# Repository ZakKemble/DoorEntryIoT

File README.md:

IoT and a Door Entry System
===========================

Adding IoT to an old apartment entry system.

https://blog.zakkemble.net/iot-and-a-door-entry-system/

---

Zak Kemble

contact@zakkemble.net

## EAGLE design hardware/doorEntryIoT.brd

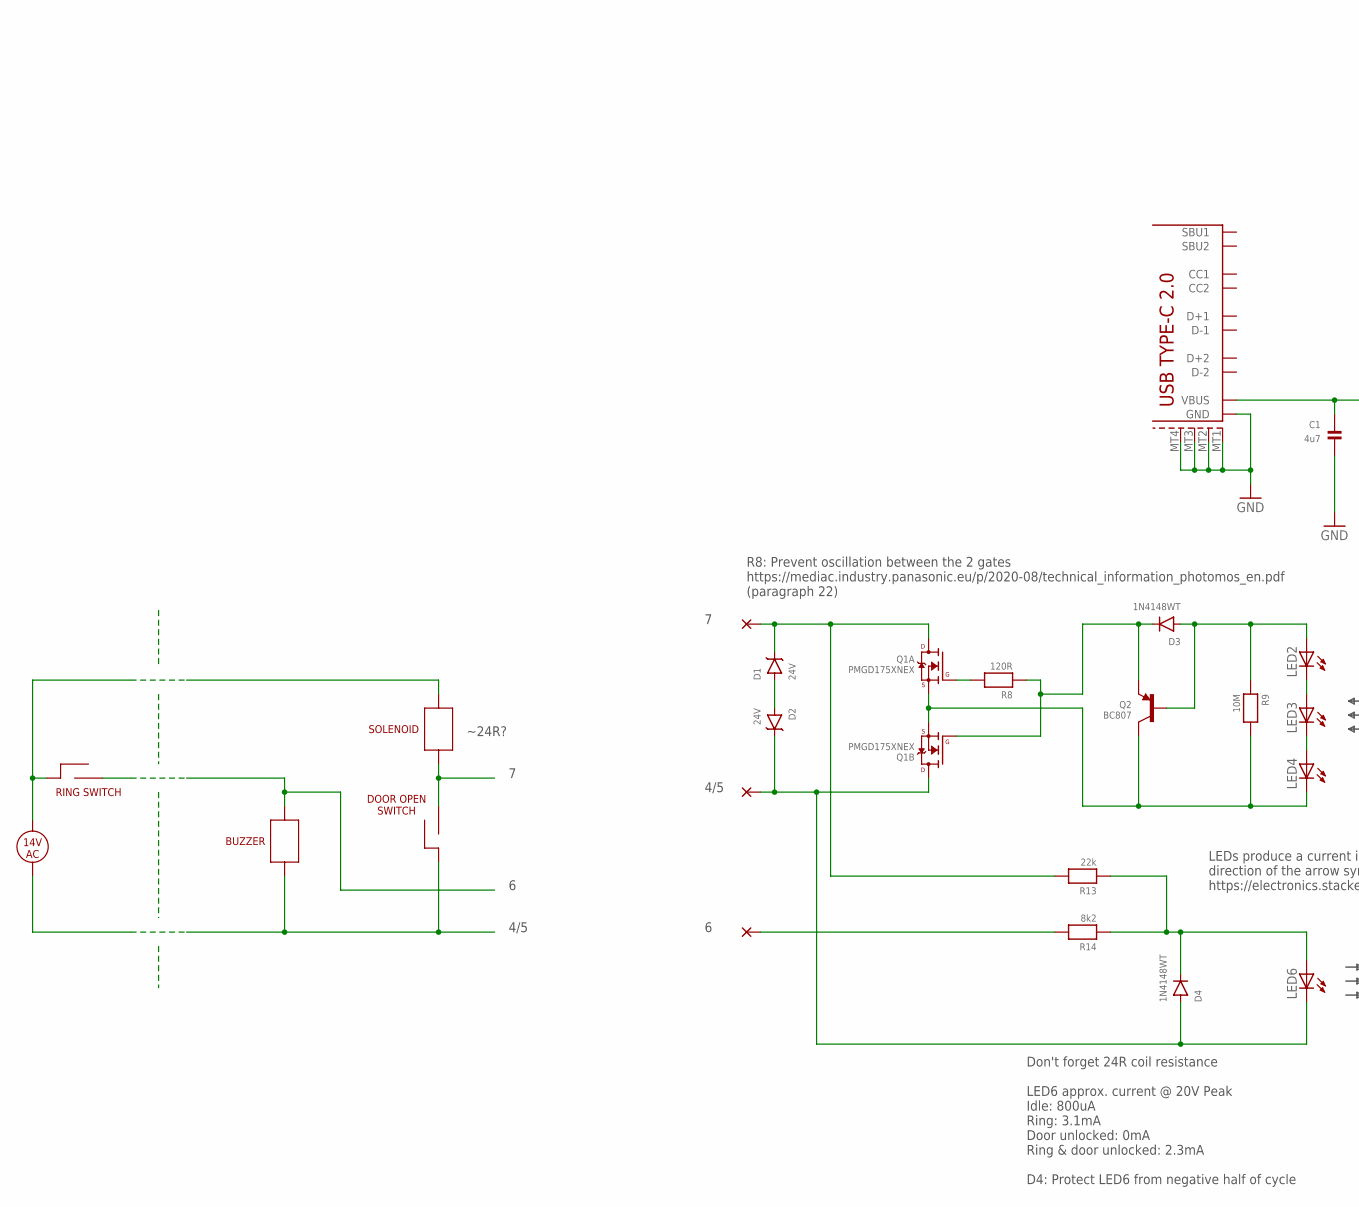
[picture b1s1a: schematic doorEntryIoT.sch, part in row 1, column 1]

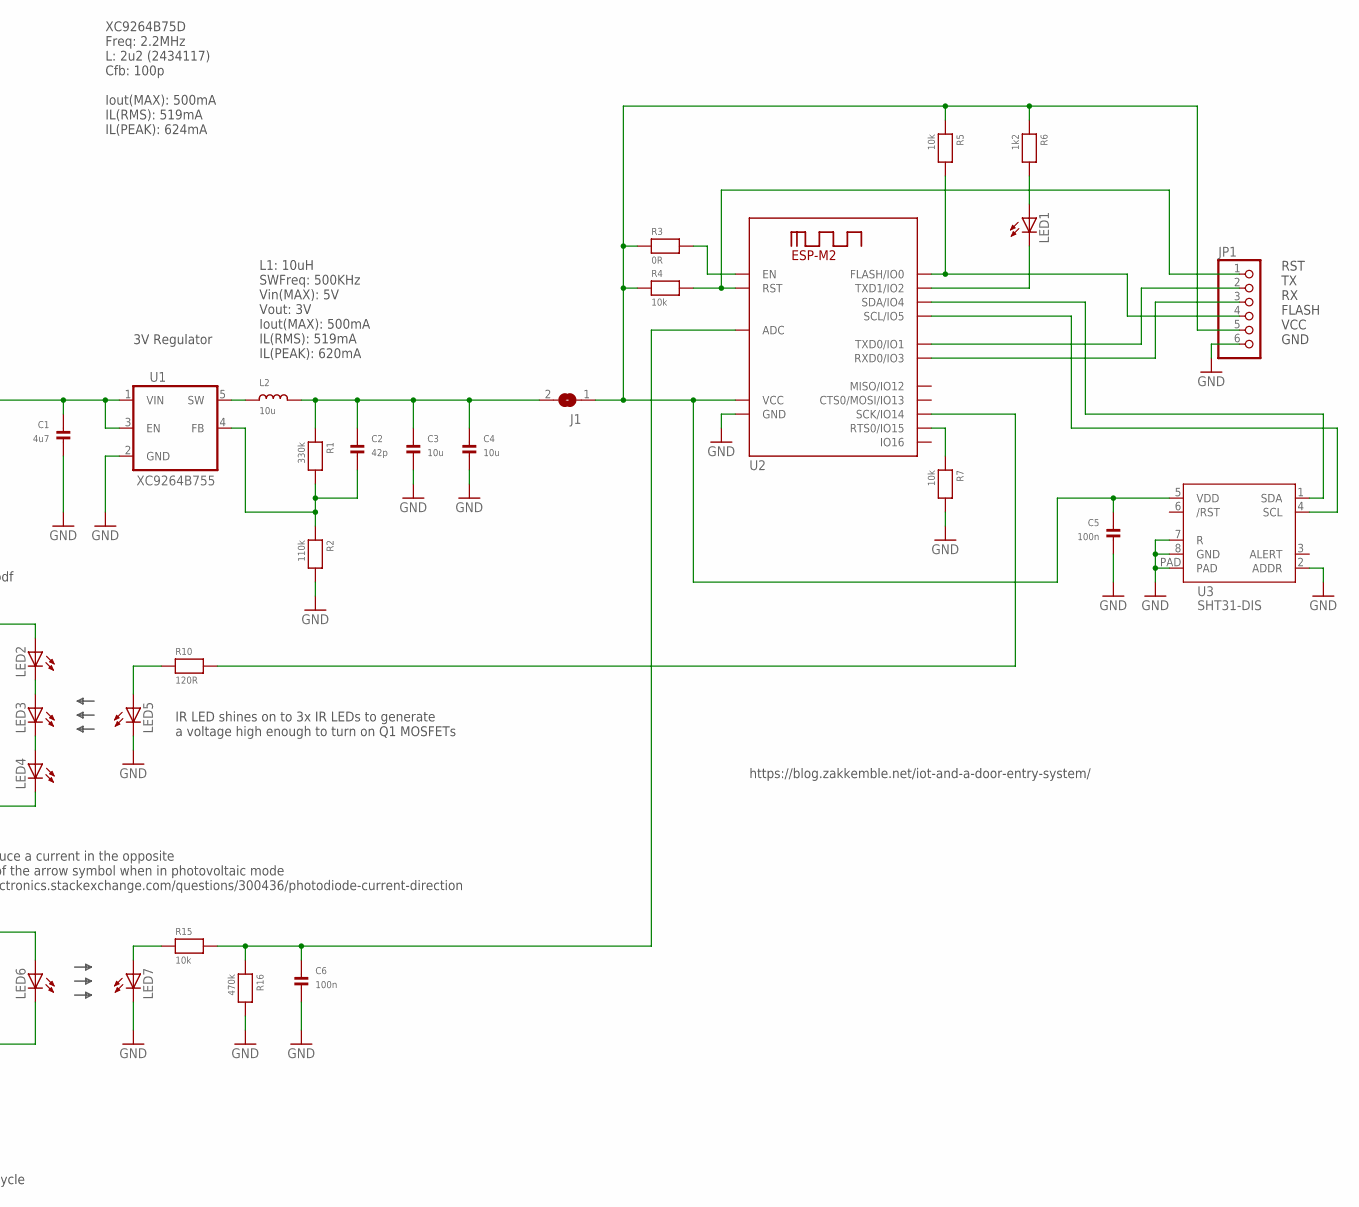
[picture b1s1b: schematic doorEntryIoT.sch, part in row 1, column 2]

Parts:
C1: 4u7; 0805_NO_OUTLINE
C2: 42p; 0402_XSMALL
C3, C4: 10u; 1206; FARNELL 9227881,1828814
C5, C6: 100n; 0402_XSMALL
D1, D2: 24V; SMA; FARNELL 1431151
D3, D4: 1N4148WT; SOD-523_SM
J1: JUMPERSMALL; JUMPER_SMALL
JP1: PINHD-1X6; 1X06
L2: 10u; 1210K; FARNELL 1463485
LED1: LED0402_XSMALL; 0402_DIODE_XSMALL
LED2, LED3, LED4, LED5, LED6, LED7: LEDSIDEVIEW; LED_SIDEVIEW; FARNELL 2426200
PAD1, PAD2, PAD3: PADSMD-1.27X2; PAD-SMD-1.27X2
Q1: PMGD175XNEX; SOT-363; FARNELL 3440057
Q2: BC807; SOT23-R
R1: 330k; 0402_XSMALL
R2: 110k; 0402_XSMALL
R3: 0R; 0402_XSMALL
R4, R5, R7, R15: 10k; 0402_XSMALL
R6: 1k2; 0402_XSMALL
R8, R10: 120R; 0402_XSMALL
R9: 10M; 0402_XSMALL
R13: 22k; 0402_XSMALL
R14: 8k2; 1206; FARNELL 1577394
R16: 470k; 0402_XSMALL
U1: XC9264B755; SOT23-5_SM_PAD; FARNELL 3535735
U2: ESP-M2
U3: SHT31-DIS; DFN_2.5X2.5_8
USB1: USB-TYPE-C-2.0SMD; USB-C-2.0_SMD

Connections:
GND: C1.2, C3.2, C4.2, C5.2, C6.2, JP1.6, LED5.1 (C), LED7.1 (C), R2.2, R7.2, R16.2, U1.2 (GND), U2.8 (GND), U3.2 (ADDR), U3.7 (R), U3.8 (GND), U3.PAD, USB1.A1B2 (GND), USB1.A12B1 (GND), USB1.MT1 (SHEILD1), USB1.MT2 (SHEILD2), USB1.MT3 (SHEILD3), USB1.MT4 (SHEILD4)
unnamed: R3.2, U2.2 (EN)
unnamed: D2.C, D4.A, LED6.1 (C), PAD2.1, Q1.3 (D)
unnamed: R10.2, U2.3 (SCK/IO14)
unnamed: C1.1, U1.1 (VIN), U1.3 (EN), USB1.A4B9 (VBUS), USB1.A9B4 (VBUS)
unnamed: U2.12 (SCL/IO5), U3.4 (SCL)
unnamed: U2.11 (SDA/IO4), U3.1 (SDA)
unnamed: Q1.2 (G), R8.2
unnamed: JP1.1, R4.2, U2.15 (RST)
unnamed: D3.K (C), Q1.5 (G), Q2.2 (E), R8.1
unnamed: C5.1, J1.1, JP1.5, R3.1, R4.1, R5.1, R6.1, U2.7 (VCC), U3.5 (VDD)
unnamed: C2.2, R1.2, R2.1, U1.4 (FB)
unnamed: L2.1, U1.5 (SW)
unnamed: LED5.2 (A), R10.1
unnamed: JP1.4, R5.2, U2.10 (FLASH/IO0)
unnamed: R7.1, U2.6 (RTS0/IO15)
unnamed: LED4.1 (C), Q1.1 (S), Q1.4 (S), Q2.3 (C), R9.2
unnamed: LED2.1 (C), LED3.2 (A)
unnamed: D1.A, D2.A
unnamed: LED1.2 (C), U2.9 (TXD1/IO2)
unnamed: LED3.1 (C), LED4.2 (A)
unnamed: JP1.2, U2.14 (TXD0/IO1)
unnamed: JP1.3, U2.13 (RXD0/IO3)
unnamed: LED1.1 (A), R6.2
unnamed: C6.1, R15.2, R16.1, U2.1 (ADC)
unnamed: D3.A, LED2.2 (A), Q2.1 (B), R9.1
unnamed: LED7.2 (A), R15.1
unnamed: D1.C, PAD3.1, Q1.6 (D), R13.2
unnamed: D4.K (C), LED6.2 (A), R13.1, R14.1
unnamed: PAD1.1, R14.2
unnamed: C2.1, C3.1, C4.1, J1.2, L2.2, R1.1

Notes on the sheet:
RST TX RX FLASH VCC GND
3V Regulator
L1: 10uH SWFreq: 500KHz Vin(MAX): 5V Vout: 3V Iout(MAX): 500mA IL(RMS): 519mA IL(PEAK): 620mA
4/5
IR LED shines on to 3x IR LEDs to generate a voltage high enough to turn on Q1 MOSFETs
Don't forget 24R coil resistance LED6 approx. current @ 20V Peak Idle: 800uA Ring: 3.1mA Door unlocked: 0mA Ring & door unlocked: 2.3mA D4: Protect LED6 from negative half of cycle
~24R?
LEDs produce a current in the opposite direction of the arrow symbol when in photovoltaic mode https://electronics.stackexchange.com/questions/300436/photodiode-current-direction
XC9264B75D Freq: 2.2MHz L: 2u2 (2434117) Cfb: 100p Iout(MAX): 500mA IL(RMS): 519mA IL(PEAK): 624mA
RING SWITCH
BUZZER
SOLENOID
DOOR OPEN SWITCH
14V AC
https://blog.zakkemble.net/iot-and-a-door-entry-system/
R8: Prevent oscillation between the 2 gates https://mediac.industry.panasonic.eu/p/2020-08/technical_information_photomos_en.pdf (paragraph 22)

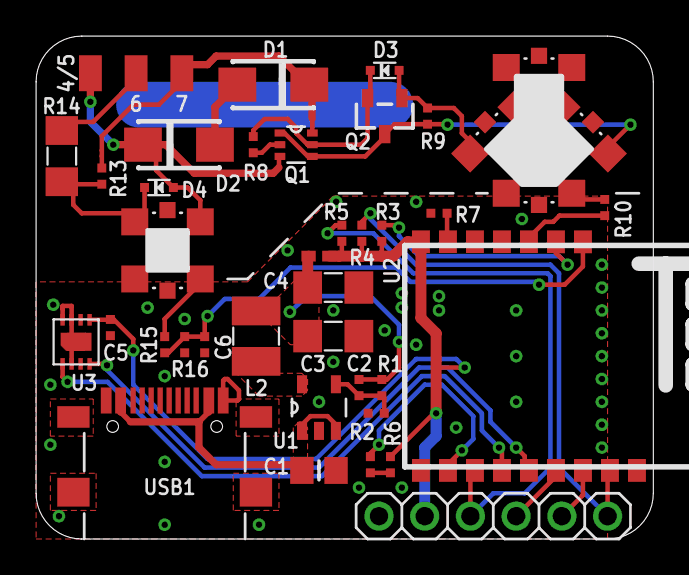
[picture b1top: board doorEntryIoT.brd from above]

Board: 2 copper layers, 34.3 x 27.9 mm, 43 parts (0 on the bottom side), 31 nets.

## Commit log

2022-02-04 Initial commit :tropical_fish:
2022-09-25 Syntactic improvements and things
    config options moved to .env file
    require to import
    functions to arrow functions
    var to let/const
2022-11-03 Add .brd and .sch linguist detection
2022-11-03 Port web app from JavaScript to TypeScript
2022-11-03 Tweaks, no need to validate UUIDs

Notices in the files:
parts and their libraries:
microbuilder: This work is placed in the public domain, and may be freely used for commercial and non-commercial work with the following conditions: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
